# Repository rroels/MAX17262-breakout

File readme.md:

# MAX17262 breakout board

> [!WARNING]
> The information and material (code, designs, files, ...) are provided "AS IS". We make no representation or warranty of any kind, express or implied, regarding the accuracy, adequacy, validity, reliability, availability, or completeness of any information or material. Use this at your own risk.

> [!WARNING]
> At the time of writing this PCB has not even been produced yet, and as such, it has not even been tested yet! Once it has been properly tested, I will confirm that everything works as expected. 

> [!WARNING]
> Note that some batteries have a "reversed" plug with the positive and negatives wires switched, so always make sure that the polarity matches the indications on the board, before plugging anything in! 

## Introduction 

I wanted to use the MAX17262 ultra-low power fuel-gauge IC in a project. However, I wanted to play around with it (at both hardware and software level), before incorporating it into a real design. 

This repository contains the design for a breakout board for the MAX17262. This board allowed me to experiment with the various hardware and software setups of this IC.

## Design Considerations

* External thermistor is not used, so `TH` is tied to `BATT`, as instructed by the datasheet.
* ALRT should be tied to GND if not used. A jumper (J4) can be used to achieve this if needed.
* I2C requires the SDA and SCL lines to have pull-up resistors ([https://learn.adafruit.com/working-with-i2c-devices/pull-up-resistors](https://learn.adafruit.com/working-with-i2c-devices/pull-up-resistors)). The board provides optional pull-up resistors. If resistors R1 and R2 are installed, they will act as pull-ups. If they are left out, the lines are left floating, or the MCU's internal pull-ups can be used. 
	* Note that we can't just "pull up" the line with with BAT+ or SYSPWR, since that voltage could be anywhere between 2 - 5v, dependending on the charge of the battery. This is problematic for a lot of reasons, the worst one being that it could destroy your microcontroller. For this reason you are expected to provide a correct voltage on the pull-up on header pin "3.3v". SDA and SCL will then be pulled up to whatever voltage is provided there (3.3V most likely, but you could use something else). 
* A Molex 53261-0271 is used, so that LiPo batteries can plugged in for testing (e.g. the types used in drones, smartwatches, ...).
* Next to the Molex connector, 2 solder pads are provided to connect a battery in other ways (e.g. directly soldering the wires to the PCB).

## Schematics

See KiCad project in this repository for a editable version of this schematic.

## BOM

|Reference|Value|Datasheet|Footprint|Qty|
|---|---|---|---|---|
|C1|0.1uF|~|Capacitor_SMD:C\_0603\_1608Metric\_Pad1.08x0.95mm\_HandSolder|1|
|C2|0.47uF|~|Capacitor_SMD:C\_0603\_1608Metric\_Pad1.08x0.95mm\_HandSolder|1|
|IC1|MAX17262HEWL+T|https://www.analog.com/MAX17262/datasheet|BGA9C40P3X3\_153X153X69:BGA9C40P3X3\_153X153X69|1|
|J1|Molex 53261-0271|~|53261-0271:532610271|1|
|J4|Conn_01x02|~|Connector\_PinHeader\_2.54mm:PinHeader\_1x02\_P2.54mm\_Vertical|1|
|J5|Conn_01x06|~|Connector\_PinHeader\_2.54mm:PinHeader\_1x06\_P2.54mm\_Horizontal|1|
|R1, R2|4.7k|~|Resistor\_SMD:R\_0603\_1608Metric\_Pad0.98x0.95mm\_HandSolder|2|

See image of the PCB below to have a better idea of what these components look like. 

All capacitors and resistors and SMD 0603. Instead of the horizontal pin header I used, a vertical pin header will also work fine (as long as the pitch is 2.54mm).

## How to Obtain the Physical PCB

The Gerber file is in this repository (`gerber/MAX17262-breakout.zip`). Simply upload this file a PCB manufacturer of your choice (JLPCB, PCBWay, ...), and you they will make it for you for as low as \$5 for 5 pieces (with the cheapest shipping option, which can take a few weeks).

> [!WARNING]
> Note that will still have to solder the components onto the PCB yourself!

## How to Edit Design

Everything you need to edit this design in KiCad 8 is included in the repository. 

However, this project uses symbols, footprints and 3D models from [Component Search Engine](https://componentsearchengine.com/). Their license allows us to do pretty much whatever we want with them, except redistributing them. For this reason I can't include them in this repository. 

If you would like to edit the design yourself, you will need to download the following component libraries from [https://componentsearchengine.com/](https://componentsearchengine.com/) (it's free!):

* [https://componentsearchengine.com/part-view/MAX17262HEWL%2BT/Analog%20Devices](https://componentsearchengine.com/part-view/MAX17262HEWL%2BT/Analog%20Devices) 

* [https://componentsearchengine.com/part-view/53261-0271/Molex
](https://componentsearchengine.com/part-view/53261-0271/Molex
)

For each downloaded zip file, move the content of the `KiCad` and `3D` subfolders into the project structure, so that the end-result looks like this:

The KiCad project is configured to look for these files in these locations, using relative paths, so no changes to the project itself are required. 

## Future Work

* Get the PCB manufactured (pending)
* Test the PCB

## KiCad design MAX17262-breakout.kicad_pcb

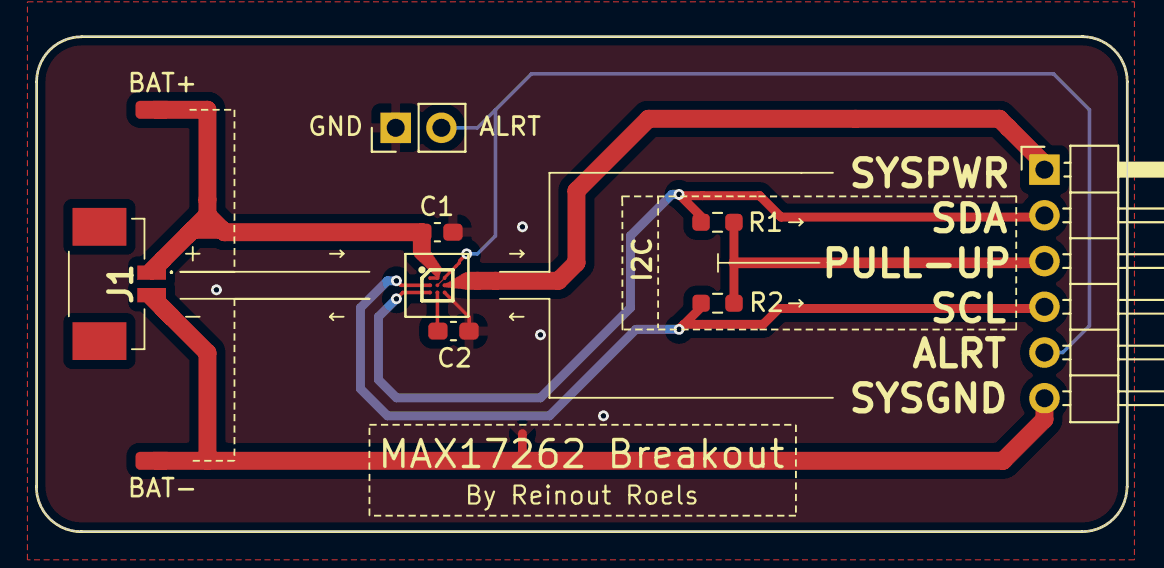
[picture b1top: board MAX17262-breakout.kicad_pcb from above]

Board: 2 copper layers, 60.6 x 27.5 mm, 11 parts (0 on the bottom side), 9 nets.

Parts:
C1: 0.1uF; C_0603_1608Metric_Pad1.08x0.95mm_HandSolder
C2: 0.47uF; C_0603_1608Metric_Pad1.08x0.95mm_HandSolder
IC1: MAX17262HEWL+T; BGA9C40P3X3_153X153X69
J1: Conn_01x02; 532610271
J2: BAT+; SolderWirePad_1x01_SMD_1x2mm
J3: BAT-; SolderWirePad_1x01_SMD_1x2mm
J4: Conn_01x02; PinHeader_1x02_P2.54mm_Vertical
J5: Conn_01x06; PinHeader_1x06_P2.54mm_Horizontal
NT1: NetTie_2; NetTie-2_SMD_Pad0.5mm
R1, R2: 4.7k; R_0603_1608Metric_Pad0.98x0.95mm_HandSolder

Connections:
ALRT: J4.2, J5.5 (ALRT)
GND: C1.2, C2.1, IC1.C3 (GND), J4.1, NT1.1
unnamed: C1.1, IC1.A1 (TH), IC1.A2 (BATT), J1.1 (BAT+), J2.1
unnamed: C2.2, IC1.C2 (REG)
unnamed: IC1.B3 (SYS), J5.1 (SYSPWR)
unnamed: J1.2 (BAT-), J3.1, J5.6 (SYSGND), NT1.2
unnamed: J5.3 (3.3v), R1.2, R2.1
SCL: IC1.B1 (SCL), J5.4 (SCL), R2.2
SDA: IC1.C1 (SDA), J5.2 (SDA), R1.1
